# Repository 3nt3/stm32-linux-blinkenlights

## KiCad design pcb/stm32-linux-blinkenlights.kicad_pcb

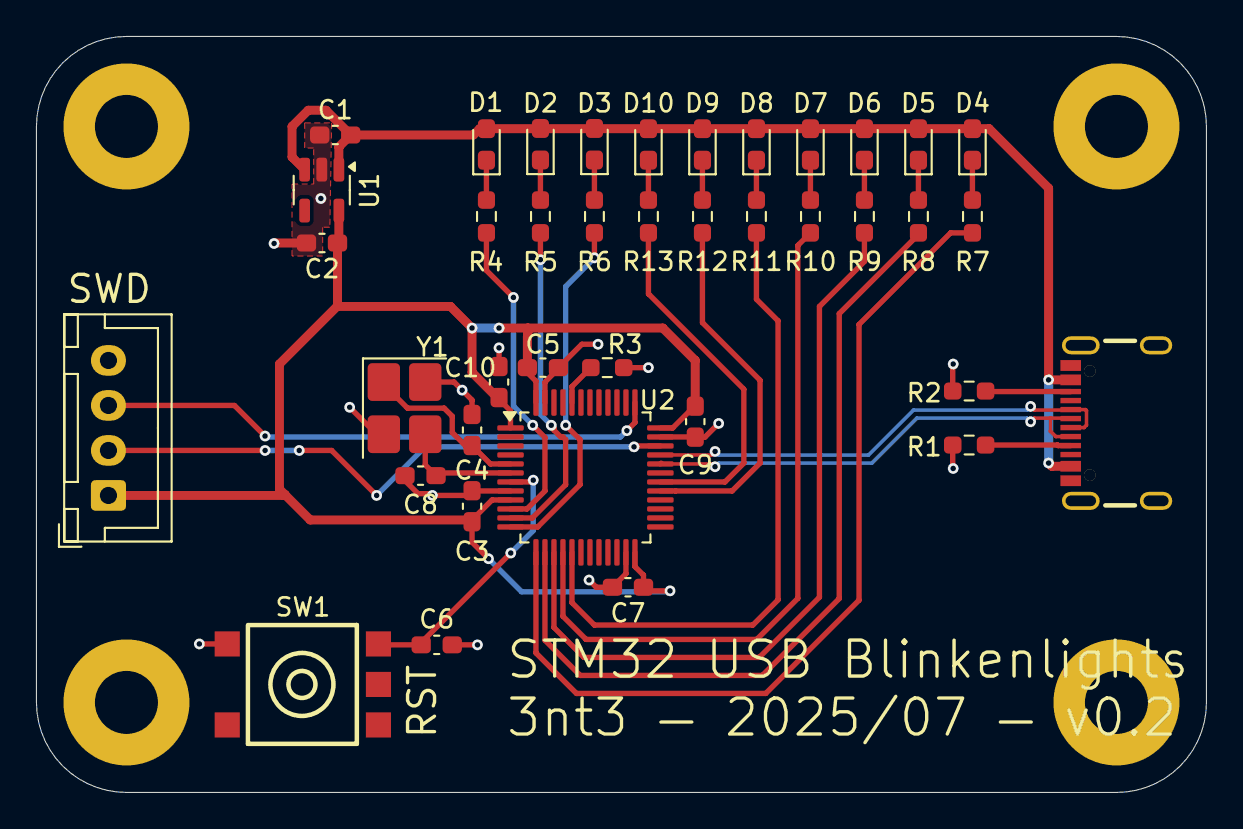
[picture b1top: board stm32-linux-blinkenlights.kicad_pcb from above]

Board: 2 copper layers, 65.0 x 42.0 mm, 43 parts (0 on the bottom side), 33 nets.

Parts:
C1, C2, C3, C5, C6, C7, C9, C10: 100n; C_0603_1608Metric_Pad1.08x0.95mm_HandSolder
C4, C8: 10p; C_0603_1608Metric_Pad1.08x0.95mm_HandSolder
D1, D2, D3, D4, D5, D6, D7, D8, D9, D10: LED; LED_0603_1608Metric_Pad1.05x0.95mm_HandSolder
H1, H2, H3, H4: MountingHole; MountingHole_3.5mm_Pad
J1: USB_C_Receptacle; USB-C-SMD_MC-311D
J2: Conn_01x04_Socket; JST_XH_B4B-XH-A_1x04_P2.50mm_Vertical
R1, R2: 5k1; R_0603_1608Metric_Pad0.98x0.95mm_HandSolder
R3: 10K; R_0603_1608Metric_Pad0.98x0.95mm_HandSolder
R4, R5, R6, R7, R8, R9, R10, R11, R12, R13: 680R; R_0603_1608Metric_Pad0.98x0.95mm_HandSolder
SW1: SW_Push; KEY-SMD_4P-L6.2-W6.5-P4.50-LS8.0_SKHMXX
U1: LP5907MFX-3.3; SOT-23-5
U2: STM32F103C8Tx; LQFP-48_7x7mm_P0.5mm
Y1: Crystal_GND24; Crystal_SMD_3225-4Pin_3.2x2.5mm_HandSoldering

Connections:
+3.3V: C2.1, C3.1, C5.1, C7.1, C9.1, C10.1, J2.1, U1.5 (OUT), U2.1 (VBAT), U2.9 (VDDA), U2.24 (VDD), U2.36 (VDD), U2.48 (VDD)
GND: C1.2, C2.2, C3.2, C4.2, C5.2, C6.2, C7.2, C8.2, C9.2, C10.2, J2.4, R1.2, R2.2, R3.1, SW1.1, U1.2 (GND), U2.8 (VSSA), U2.23 (VSS), U2.35 (VSS), U2.47 (VSS), Y1.2, Y1.4
LED_1: R4.2, U2.10 (PA0)
LED_2: R5.2, U2.11 (PA1)
LED_3: R6.2, U2.12 (PA2)
LED_4: R7.2, U2.13 (PA3)
LED_5: R8.2, U2.14 (PA4)
LED_6: R9.2, U2.15 (PA5)
LED_7: R10.2, U2.16 (PA6)
LED_8: R11.2, U2.17 (PA7)
LED_9: R12.2, U2.29 (PA8)
LED_10: R13.2, U2.30 (PA9)
unnamed: D1.1 (K), R4.1
unnamed: D2.1 (K), R5.1
unnamed: D3.1 (K), R6.1
unnamed: D4.1 (K), R7.1
unnamed: D5.1 (K), R8.1
unnamed: D6.1 (K), R9.1
unnamed: D7.1 (K), R10.1
unnamed: D8.1 (K), R11.1
unnamed: D9.1 (K), R12.1
unnamed: D10.1 (K), R13.1
unnamed: J1.A5 (CC1), R1.1
unnamed: J1.B5 (CC2), R2.1
unnamed: J2.2, U2.34 (PA13)
unnamed: J2.3, U2.37 (PA14)
unnamed: R3.2, U2.44 (BOOT0)
unnamed: C6.1, SW1.2, U2.7 (NRST)
unnamed: C4.1, U2.5 (PD0), Y1.1
unnamed: C8.1, U2.6 (PD1), Y1.3
USB_D+: J1.A6 (D+), J1.B6 (D+), U2.33 (PA12)
USB_D-: J1.A7 (D-), J1.B7 (D-), U2.32 (PA11)
VBUS: C1.1, D1.2 (A), D2.2 (A), D3.2 (A), D4.2 (A), D5.2 (A), D6.2 (A), D7.2 (A), D8.2 (A), D9.2 (A), D10.2 (A), U1.1 (IN), U1.3 (EN)

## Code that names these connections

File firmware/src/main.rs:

#![no_std]
#![no_main]

mod fmt;

use defmt::info;
use embassy_executor::Spawner;
use embassy_futures::join::join;
use embassy_stm32::gpio::{OutputOpenDrain, OutputType};
use embassy_stm32::Config;
use embassy_stm32::{
    bind_interrupts,
    gpio::{Level, Output, Speed},
    peripherals,
    time::Hertz,
};
use embassy_time::Timer;
use embassy_usb::{
    class::cdc_acm::{CdcAcmClass, State},
    driver::EndpointError,
    Builder,
};
#[cfg(not(feature = "defmt"))]
use panic_halt as _;
use panic_probe as _;
#[cfg(feature = "defmt")]
use {defmt_rtt as _, panic_probe as _};

bind_interrupts!(struct Irqs {
    USB_LP_CAN1_RX0 => embassy_stm32::usb::InterruptHandler<peripherals::USB>;
});

mod logic;
mod usb;

#[embassy_executor::main]
async fn main(_spawner: Spawner) {
    let mut config = Config::default();
    {
        use embassy_stm32::rcc::*;
        config.rcc.hse = Some(Hse {
            freq: Hertz(8_000_000),
            // Oscillator for bluepill, Bypass for nucleos.
            mode: HseMode::Oscillator,
        });
        config.rcc.pll = Some(Pll {
            src: PllSource::HSE,
            prediv: PllPreDiv::DIV1,
            mul: PllMul::MUL9,
        });
        config.rcc.sys = Sysclk::PLL1_P;
        config.rcc.ahb_pre = AHBPrescaler::DIV1;
        config.rcc.apb1_pre = APBPrescaler::DIV2;
        config.rcc.apb2_pre = APBPrescaler::DIV1;
    }

    let mut p = embassy_stm32::init(config);

    info!("Hello World!");

    {
        // BluePill board has a pull-up resistor on the D+ line.
        // Pull the D+ pin down to send a RESET condition to the USB bus.
        // This forced reset is needed only for development, without it host
        // will not reset your device when you upload new firmware.
        let _dp = Output::new(&mut p.PA12, Level::Low, Speed::Low);
        Timer::after_millis(10).await;
    }

    let usb_driver = embassy_stm32::usb::Driver::new(p.USB, Irqs, p.PA12, p.PA11);

    let mut usb_config = embassy_usb::Config::new(0xffff, 0xffff);
    usb_config.manufacturer = Some("3nt3");
    usb_config.product = Some("STM32 USB Blinkenlights");

    let mut config_descriptor = [0; 256];
    let mut bos_descriptor = [0; 256];
    let mut control_buf = [0; 256];

    let mut state = State::new();

    let mut builder = Builder::new(
        usb_driver,
        usb_config,
        &mut config_descriptor,
        &mut bos_descriptor,
        &mut [],
        &mut control_buf,
    );

    let mut class = CdcAcmClass::new(&mut builder, &mut state, 64);

    let mut usb = builder.build();

    let usb_fut = usb.run();

    let mut leds = [
        OutputOpenDrain::new(&mut p.PA0, Level::Low, Speed::Low),
        OutputOpenDrain::new(&mut p.PA1, Level::Low, Speed::Low),
        OutputOpenDrain::new(&mut p.PA2, Level::Low, Speed::Low),
        OutputOpenDrain::new(&mut p.PA3, Level::Low, Speed::Low),
        OutputOpenDrain::new(&mut p.PA4, Level::Low, Speed::Low),
        OutputOpenDrain::new(&mut p.PA5, Level::Low, Speed::Low),
        OutputOpenDrain::new(&mut p.PA6, Level::Low, Speed::Low),
        OutputOpenDrain::new(&mut p.PA7, Level::Low, Speed::Low),
        OutputOpenDrain::new(&mut p.PA8, Level::Low, Speed::Low),
        OutputOpenDrain::new(&mut p.PA9, Level::Low, Speed::Low),
    ];

    let usb_logic_fut = usb::usb_task(&mut class, &mut leds);

    join(usb_fut, usb_logic_fut).await;
}

struct Disconnected {}

impl From<EndpointError> for Disconnected {
    fn from(val: EndpointError) -> Self {
        match val {
            EndpointError::BufferOverflow => panic!("Buffer overflow"),
            EndpointError::Disabled => Disconnected {},
        }
    }
}

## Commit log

2025-07-03 update pcb
2025-07-05 make usb work!!!
2025-07-05 remove target??
2025-07-05 make led blink
2025-07-06 add more things to gitignore
2025-07-06 protocol things
2025-07-06 move protocol logic into seperate crate
2025-07-06 everything kinda works
2025-07-06 implement basic client
2025-07-07 add more driver things
2025-07-16 v0.2?
